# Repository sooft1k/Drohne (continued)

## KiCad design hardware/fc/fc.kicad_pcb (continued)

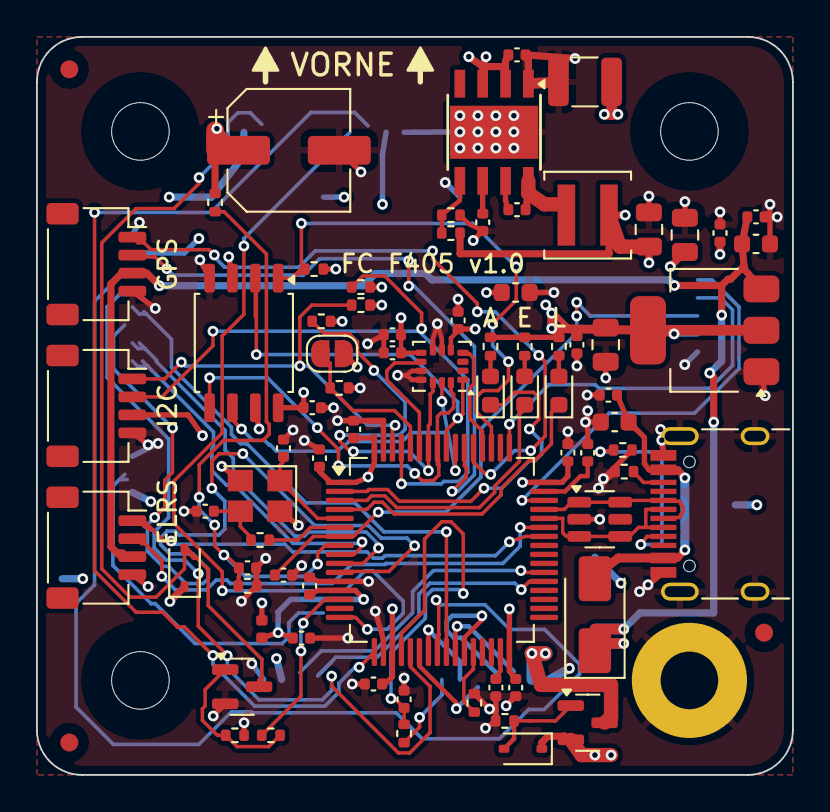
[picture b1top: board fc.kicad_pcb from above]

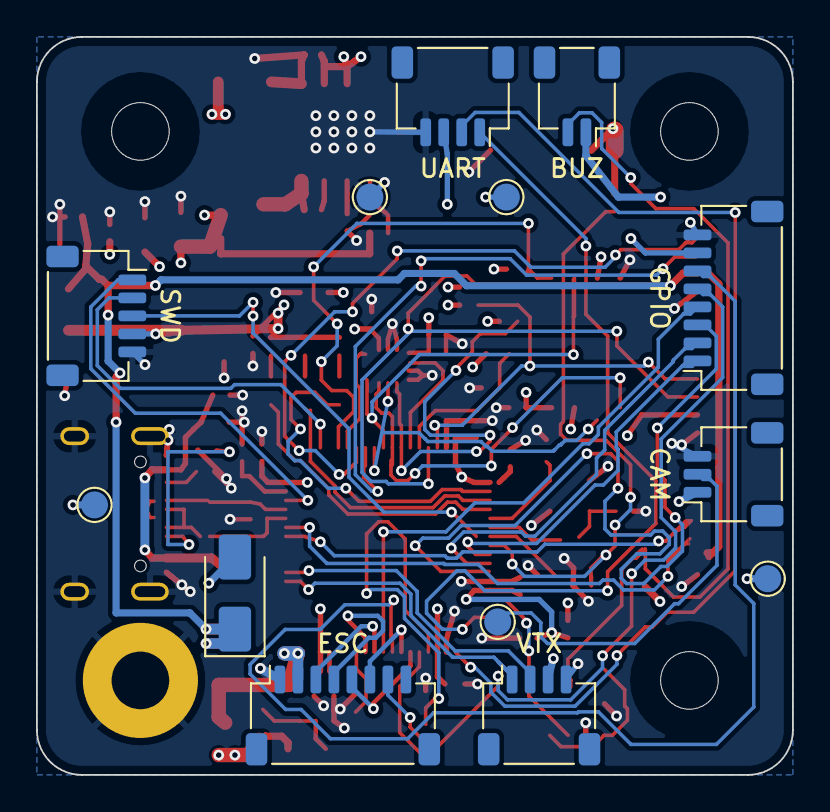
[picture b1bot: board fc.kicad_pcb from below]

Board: 4 copper layers, 42.0 x 41.0 mm, 95 parts (13 on the bottom side), 67 nets.

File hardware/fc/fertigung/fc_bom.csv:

Comment,Designator,Footprint,Hersteller-Nr.,Anzahl,Bestueckung
100nF,"C1,C2,C3,C4,C5,C7,C11,C14,C15,C16,C18,C20,C24,C28,C30,C32,C34",C_0402_1005Metric,,17,oben (JLCPCB)
4.7uF,C6,C_0603_1608Metric,,1,oben (JLCPCB)
1uF,"C8,C25",C_0402_1005Metric,,2,oben (JLCPCB)
2.2uF,"C9,C10,C17",C_0402_1005Metric,,3,oben (JLCPCB)
18pF,"C12,C13",C_0402_1005Metric,,2,oben (JLCPCB)
470uF/35V,C21,CP_Elec_10x10.5,EEE-FK1V471P,1,oben (JLCPCB)
10uF/50V,C22,C_1210_3225Metric,,1,oben (JLCPCB)
100nF/50V,C23,C_0402_1005Metric,,1,oben (JLCPCB)
22uF/16V,"C26,C27",C_0805_2012Metric,,2,oben (JLCPCB)
10uF,"C29,C33",C_0603_1608Metric,,2,oben (JLCPCB)
22uF,C31,C_0805_2012Metric,,1,oben (JLCPCB)
BZT52C15S,D1,D_SOD-323,BZT52C15S,1,oben (JLCPCB)
SS14,D2,D_SMA,SS14,1,oben (JLCPCB)
rot,D3,LED_0603_1608Metric,,1,oben (JLCPCB)
gelb,D4,LED_0603_1608Metric,,1,oben (JLCPCB)
gruen,D5,LED_0603_1608Metric,,1,oben (JLCPCB)
1N4148WS,D6,D_SOD-323,,1,oben (JLCPCB)
600R@100MHz,FB1,L_0402_1005Metric,BLM15AG601SN1D,1,oben (JLCPCB)
USB-C,J1,USB_C_Receptacle_HRO_TYPE-C-31-M-12_Kante,TYPE-C-31-M-12,1,oben (JLCPCB)
ESC,J2,JST_SH_SM08B-SRSS-TB_1x08-1MP_P1.00mm_Horizontal,SM08B-SRSS-TB,1,"unten, von Hand"
ELRS,J3,PinHeader_1x04_P2.54mm_Vertical_SMD_Pin1Left,,1,"unten, von Hand"
I2C,J4,PinHeader_1x04_P2.54mm_Vertical_SMD_Pin1Left,,1,"unten, von Hand"
GPS,J5,PinHeader_1x04_P2.54mm_Vertical_SMD_Pin1Left,,1,"unten, von Hand"
VTX,J6,PinHeader_1x04_P2.54mm_Vertical_SMD_Pin1Left,,1,"unten, von Hand"
CAM,J7,PinHeader_1x03_P2.54mm_Vertical_SMD_Pin1Left,,1,"unten, von Hand"
SWD,J8,PinHeader_1x05_P2.54mm_Vertical_SMD_Pin1Left,,1,"unten, von Hand"
UART,J9,PinHeader_1x04_P2.54mm_Vertical_SMD_Pin1Left,,1,"unten, von Hand"
GPIO,J10,PinHeader_1x08_P2.54mm_Vertical_SMD_Pin1Left,,1,"unten, von Hand"
BUZZER,J11,PinHeader_1x02_P2.54mm_Vertical_SMD_Pin1Left,,1,"unten, von Hand"
3.3uH,L1,L_Coilcraft_XAL4040-XXX,XAL4040-332MEB,1,oben (JLCPCB)
Si2319CDS,Q1,SOT-23,SI2319CDS-T1-GE3,1,oben (JLCPCB)
2N7002,Q2,SOT-23,,1,oben (JLCPCB)
10k,"R1,R2,R4,R7,R8,R18",R_0402_1005Metric,,6,oben (JLCPCB)
0R,R3,R_0402_1005Metric,,1,oben (JLCPCB)
1k,"R5,R6,R14,R15,R16",R_0402_1005Metric,,5,oben (JLCPCB)
100k,"R9,R10",R_0402_1005Metric,,2,oben (JLCPCB)
24.9k,R11,R_0402_1005Metric,,1,oben (JLCPCB)
5.1k,"R12,R13",R_0402_1005Metric,,2,oben (JLCPCB)
100R,R17,R_0402_1005Metric,,1,oben (JLCPCB)
4.7k,"R19,R20",R_0402_1005Metric,,2,oben (JLCPCB)
STM32F405RGT6,U1,LQFP-64_10x10mm_P0.5mm,STM32F405RGT6,1,oben (JLCPCB)
ICM-42688-P,U2,LGA-14_3x2.5mm_P0.5mm_LayoutBorder3x4y,ICM-42688-P,1,oben (JLCPCB)
W25Q128JVSIQ,U3,SOIC-8_5.23x5.23mm_P1.27mm,W25Q128JVSIQ,1,oben (JLCPCB)
LMR33630BDDA,U4,Texas_HSOP-8-1EP_3.9x4.9mm_P1.27mm_ThermalVias_TopOnly,LMR33630BDDAR,1,oben (JLCPCB)
AMS1117-3.3,U5,SOT-223-3_TabPin2,AMS1117-3.3,1,oben (JLCPCB)
USBLC6-2SC6,U6,SOT-23-6,USBLC6-2SC6,1,oben (JLCPCB)
8MHz,Y1,Crystal_SMD_3225-4Pin_3.2x2.5mm,X322508MSB4SI,1,oben (JLCPCB)

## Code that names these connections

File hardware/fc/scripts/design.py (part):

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# ---------------------------------------------------------------- Prozessor
MCU_PINS = {
    '1': '+3V3',        # VBAT (kein RTC-Akku) an 3,3 V
    '2': 'LED_ARM',     # PC13 (LED aktiv-low, Pin zieht nur Strom)
    '3': 'LED_ERR',     # PC14 (LED aktiv-low)
    '4': 'LED_LINK',    # PC15 (LED aktiv-low)
    '5': 'OSC_IN',      # PH0
    '6': 'OSC_OUT',     # PH1
    '7': 'NRST',
    '8': 'VBAT_SENSE',  # PC0  ADC1_IN10 (fest)
    '9': 'GPIO1',       # PC1
    '10': 'GPIO2',      # PC2
    '11': 'GPIO3',      # PC3
    '12': 'GND',        # VSSA
    '13': '+3V3A',      # VDDA (VREF+ intern, LQFP64)
    '14': 'BUZZER',     # PA0  TIM2_CH1 / TIM5_CH1
    '15': None,         # PA1  (frei; Pad laesst sich zwischen BUZZER/DBG_TX nicht entflechten)
    '16': 'DBG_TX',     # PA2  USART2_TX
    '17': 'DBG_RX',     # PA3  USART2_RX
    '18': 'GND',        # VSS
    '19': '+3V3',       # VDD
    '20': 'CURR_SENSE', # PA4  ADC12_IN4
    '21': 'GPIO5',      # PA5
    '22': 'M3',         # PA6  TIM3_CH1
    '23': 'M4',         # PA7  TIM3_CH2
    '24': 'GPIO6',      # PC4
    '25': 'GPIO4',      # PC5
    '26': 'M1',         # PB0  TIM3_CH3 (Motorpins wie in der Firmware, Sensors/motor.c)
    '27': 'M2',         # PB1  TIM3_CH4
    '28': 'BOOT1',      # PB2 / BOOT1 -> 10k nach GND
    '29': None,         # PB10
    '30': None,         # PB11
    '31': 'VCAP1',
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    '34': None,         # PB13
    '35': None,         # PB14
    '36': None,         # PB15
    '37': 'VTX_TX',     # PC6  USART6_TX
    '38': 'VTX_RX',     # PC7  USART6_RX
    '39': None,         # PC8
    '40': None,         # PC9
    '41': None,         # PA8
    '42': 'ELRS_TX',    # PA9  USART1_TX
    '43': 'ELRS_RX',    # PA10 USART1_RX
    '44': 'USB_DM',     # PA11
    '45': 'USB_DP',     # PA12
    '46': 'SWDIO',      # PA13
    '47': 'VCAP2',
    '48': '+3V3',       # VDD
    '49': 'SWCLK',      # PA14
    '50': None,         # PA15
    '51': 'FLASH_CS',   # PC10
    '52': 'GYRO_INT1',  # PC11 EXTI11
    '53': 'GPS_TX',     # PC12 UART5_TX
    '54': 'GPS_RX',     # PD2  UART5_RX
    '55': 'SPI1_SCK',   # PB3
    '56': 'SPI1_MISO',  # PB4
    '57': 'SPI1_MOSI',  # PB5
    '58': 'GYRO_CS',    # PB6
    '59': 'GYRO_INT2',  # PB7  TIM4_CH2 (CLKIN moeglich)
    '60': 'BOOT0',
    '61': 'I2C_SCL',    # PB8  I2C1_SCL
    '62': 'I2C_SDA',    # PB9  I2C1_SDA
    '63': 'GND',        # VSS
    '64': '+3V3',       # VDD
}
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R('R1', '10k', 'BOOT0', 'GND', 'mcu', 'BOOT0 Pull-down')
part('JP1', 'Jumper:SolderJumper_2_Open', 'BOOT0', SJ_OPEN,
     {'1': 'BOOT0', '2': '+3V3'}, 'mcu', 'Loetbruecke: geschlossen = DFU-Bootloader')
R('R2', '10k', 'BOOT1', 'GND', 'mcu', 'PB2/BOOT1 Pull-down (fuer DFU)')
part('Y1', 'Device:Crystal_GND24', '8MHz', 'Crystal:Crystal_SMD_3225-4Pin_3.2x2.5mm',
     {'1': 'OSC_IN', '2': 'GND', '3': 'XTAL_OUT', '4': 'GND'}, 'mcu',
     'Quarz 8 MHz, CL 12 pF', 'XL2OI-111-8M')
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     {'1': 'DBG_TX', '2': 'DBG_RX', '3': '+3V3', '4': 'GND'}, 'conn',
     'Debug-UART', side='bottom')
part('J10', 'Connector_Generic:Conn_01x08', 'GPIO', SH % (8, 8),
     {'1': 'GPIO1', '2': 'GPIO2', '3': 'GPIO3', '4': 'GPIO4', '5': 'GPIO5',
      '6': 'GPIO6', '7': '+3V3', '8': 'GND'}, 'conn', 'Freie GPIOs (XSHUT)',
     side='bottom')
part('TP5', 'Connector:TestPoint', 'VIDEO', TP_PAD, {'1': 'CAM_VIDEO'}, 'conn',
     'Video-Durchleitung zum analogen VTX', side='bottom')
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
